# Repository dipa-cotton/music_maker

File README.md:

# Music Maker

this is my music maker! it's a 3 part midi keyboard/synth that has a LOT of thought put into it. It's able to connect using magnetic pogo connectors, has 2 outputs, communicates via xiao nrf5820, and has so so so many switches, sliders, and rotary encoders!

these 2 parts connect together to form an octave, yay!

this is the synth that connects to the edge of the board.

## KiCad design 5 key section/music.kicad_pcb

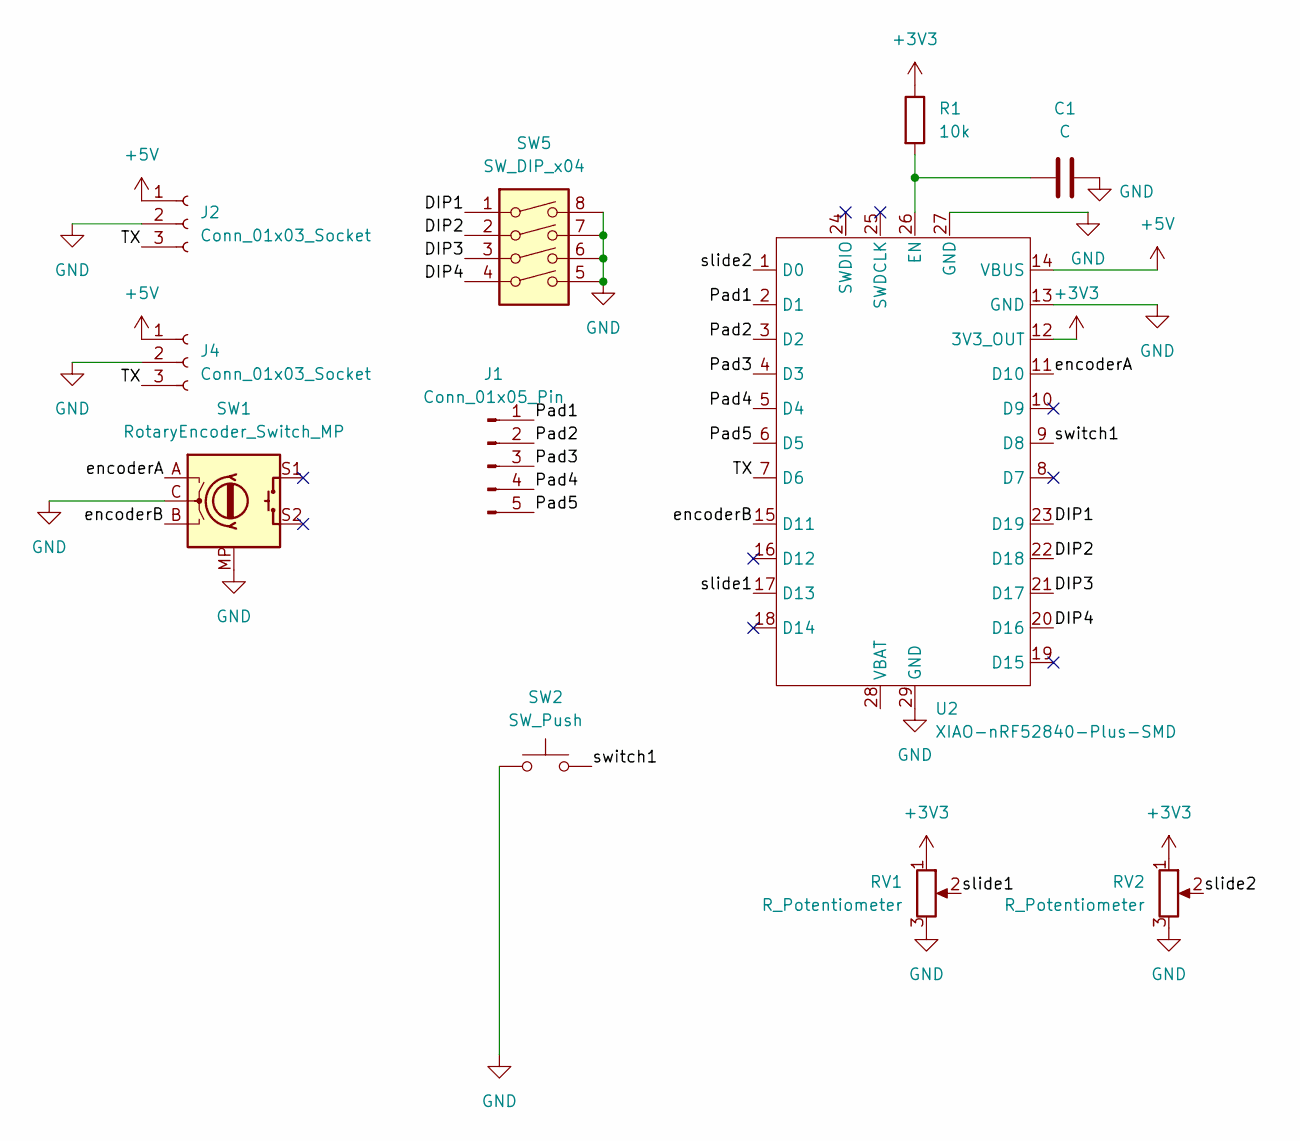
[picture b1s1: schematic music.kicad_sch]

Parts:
C1: C; CP_Axial_L10.0mm_D4.5mm_P15.00mm_Horizontal
J1: Conn_01x05_Pin; keys_real!
J2, J4: Conn_01x03_Socket; PinHeader_1x03_P2.54mm_Vertical
R1: 10k; R_Axial_DIN0204_L3.6mm_D1.6mm_P5.08mm_Horizontal
RV1, RV2: R_Potentiometer; Potentiometer_Bourns_PTA1543_Single_Slide
SW1: RotaryEncoder_Switch_MP; RotaryEncoder_Alps_EC11E-Switch_Vertical_H20mm
SW2: SW_Push; SW_Cherry_MX_1.00u_PCB
SW5: SW_DIP_x04; DIP-8_W10.16mm
U2: XIAO-nRF52840-Plus-SMD

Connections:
+3V3: R1.1, RV1.1, RV2.1, U2.12 (3V3_OUT)
+5V: J2.1, J4.1, U2.14 (VBUS)
/DIP1: SW5.1, U2.23 (D19)
/DIP2: SW5.2, U2.22 (D18)
/DIP3: SW5.3, U2.21 (D17)
/DIP4: SW5.4, U2.20 (D16)
/Pad1: J1.1, U2.2 (D1)
/Pad2: J1.2, U2.3 (D2)
/Pad3: J1.3, U2.4 (D3)
/Pad4: J1.4, U2.5 (D4)
/Pad5: J1.5, U2.6 (D5)
/TX: J2.3, J4.3, U2.7 (D6)
/encoderA: SW1.A, U2.11 (D10)
/encoderB: SW1.B, U2.15 (D11)
/slide1: RV1.2, U2.17 (D13)
/slide2: RV2.2, U2.1 (D0)
/switch1: SW2.2, U2.9 (D8)
GND: C1.2, J2.2, J4.2, RV1.3, RV2.3, SW1.C, SW1.MP, SW2.1, SW5.5, SW5.6, SW5.7, SW5.8, U2.13 (GND), U2.27 (GND), U2.29 (GND)
unnamed: C1.1, R1.2, U2.26 (EN)

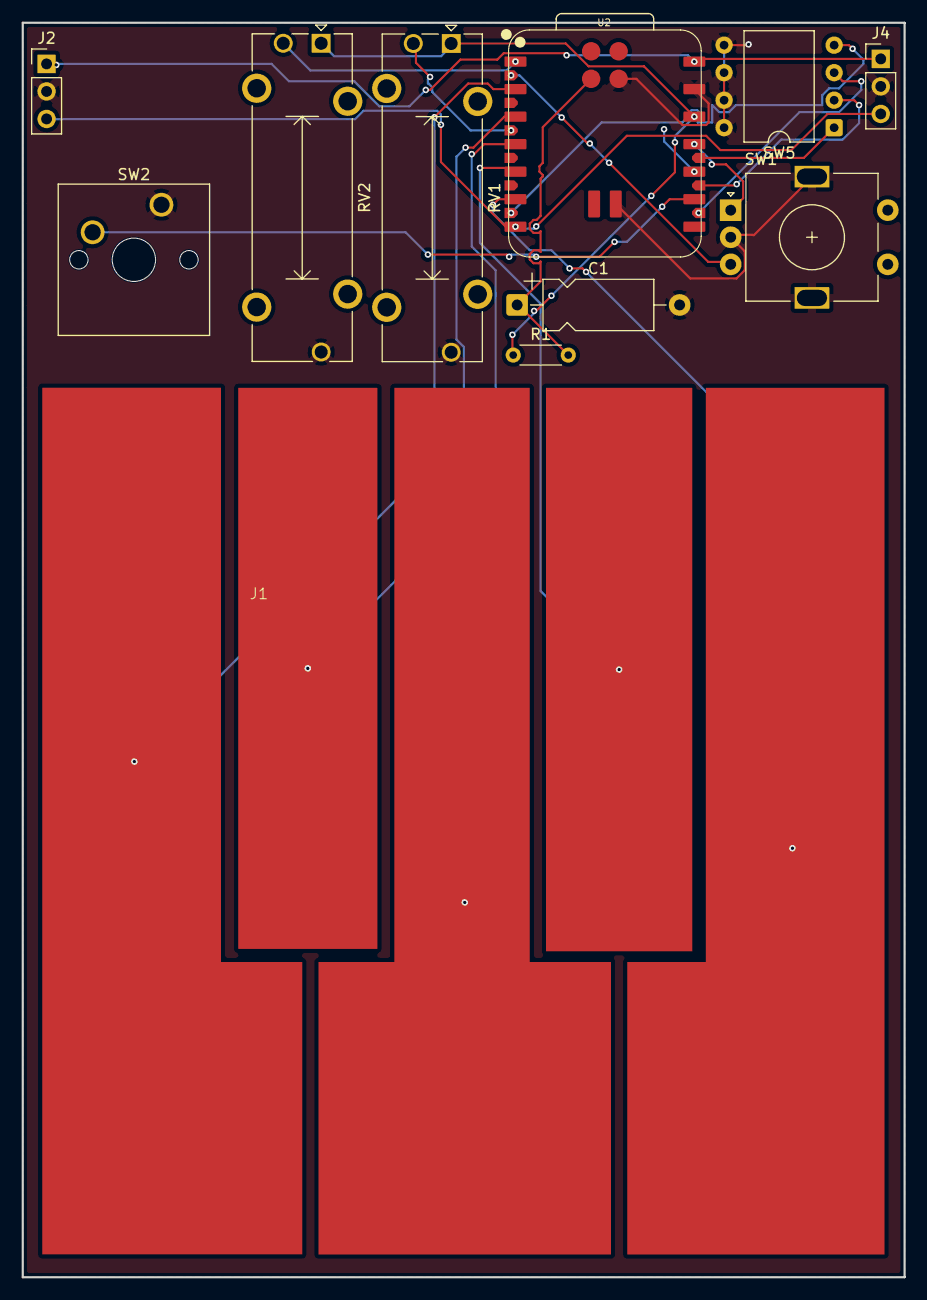
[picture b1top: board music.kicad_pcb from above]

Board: 2 copper layers, 81.4 x 115.8 mm, 11 parts (0 on the bottom side), 19 nets.
